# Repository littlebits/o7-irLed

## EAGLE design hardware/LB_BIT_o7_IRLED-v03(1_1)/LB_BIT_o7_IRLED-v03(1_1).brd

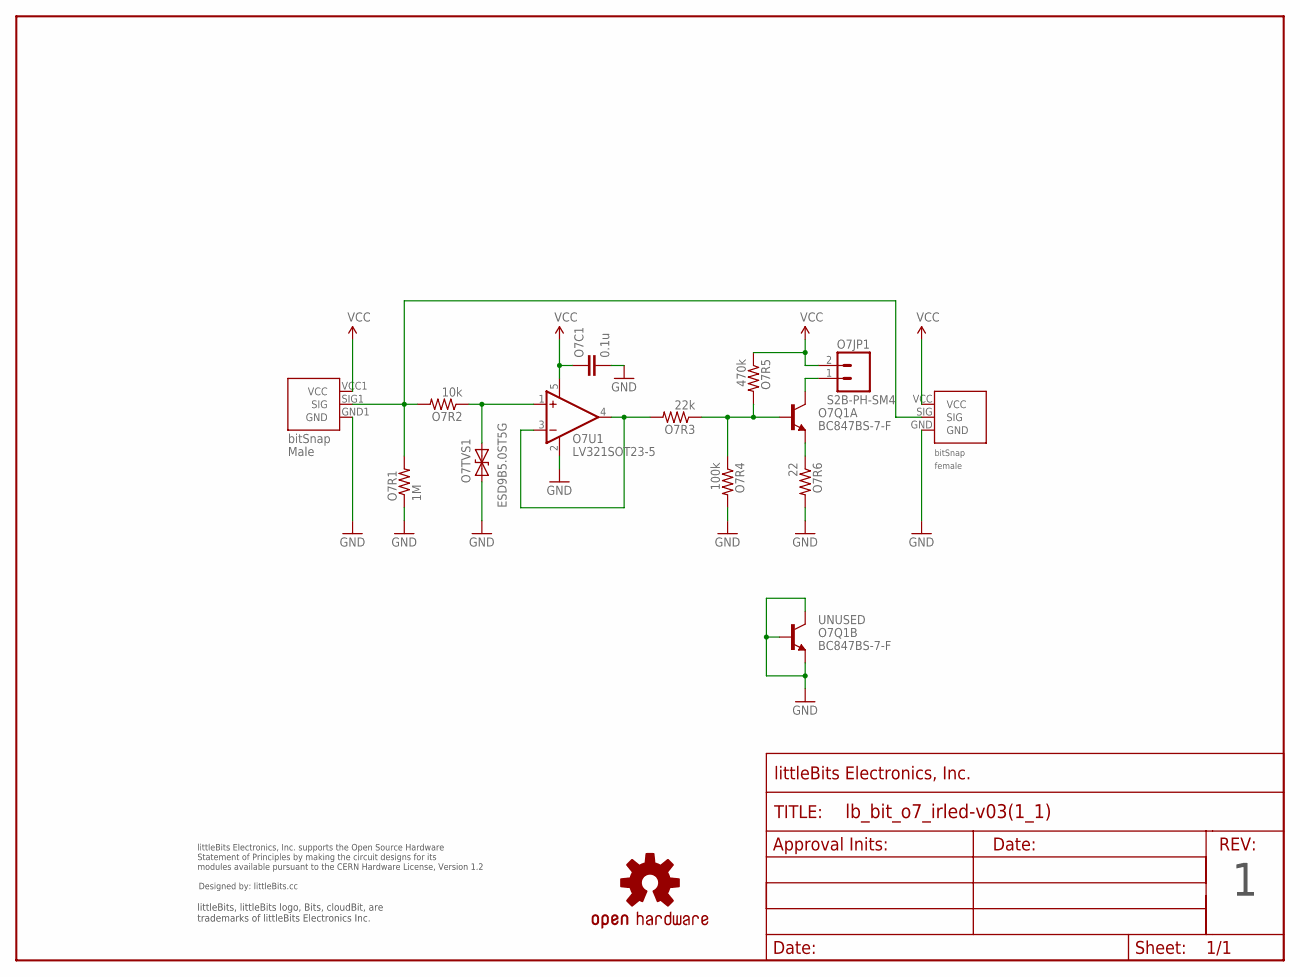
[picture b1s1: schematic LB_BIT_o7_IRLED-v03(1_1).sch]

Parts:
O7BSF1: BITSNAP_V03_FEMALE
O7BSM1: BITSNAP_V03_MALE
O7C1: 0.1u; CAP-0603
O7JP1: S2B-PH-SM4; S2B-PH
O7Q1: BC847BS-7-F; SOT-363_PHILLIPS
O7R1: 1M; RES-0603
O7R2: 10k; RES-0603
O7R3: 22k; RES-0603
O7R4: 100k; RES-0603
O7R5: 470k; RES-0603
O7R6: 22; RES-0603
O7TVS1: ESD9B5.0ST5G; SOD-923
O7U1: LV321SOT23-5; SOT23-5
U$5: FRAME-LETTER-OHWOHW; FABDWG01-OHW
U$8: OSHWCREDIT
U$14: OSHW-LOGOL; OSHW-LOGO-L

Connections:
GND: O7BSF1.GND, O7BSM1.GND1 (GND), O7C1.2, O7Q1.3 (C), O7Q1.4 (E), O7Q1.5 (B), O7R1.1, O7R4.2, O7R6.2, O7TVS1.1 (A), O7U1.2 (V-)
unnamed: O7JP1.1, O7Q1.6 (C)
unnamed: O7Q1.1 (E), O7R6.1
unnamed: O7Q1.2 (B), O7R3.1, O7R4.1, O7R5.2
unnamed: O7R2.1, O7TVS1.2 (C), O7U1.1 (+IN)
unnamed: O7BSF1.SIG, O7BSM1.SIG1 (SIG), O7R1.2, O7R2.2
unnamed: O7R3.2, O7U1.3 (-IN), O7U1.4 (OUT)
VCC: O7BSF1.VCC, O7BSM1.VCC1 (VCC), O7C1.1, O7JP1.2, O7R5.1, O7U1.5 (V+)

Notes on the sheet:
UNUSED

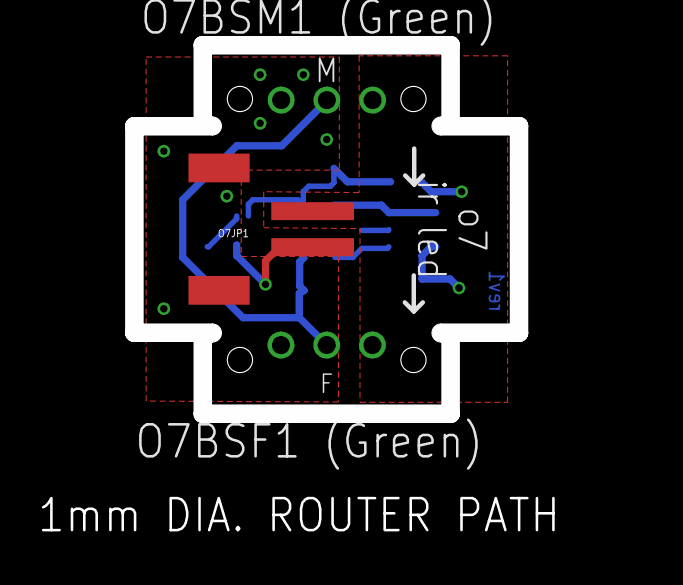
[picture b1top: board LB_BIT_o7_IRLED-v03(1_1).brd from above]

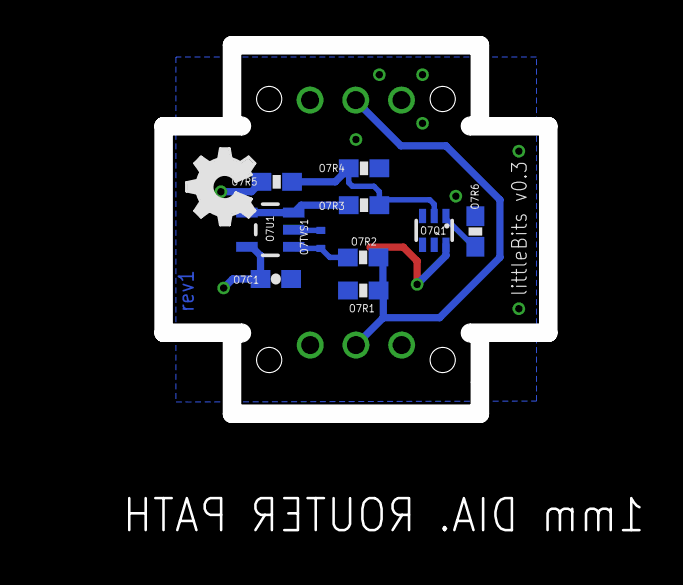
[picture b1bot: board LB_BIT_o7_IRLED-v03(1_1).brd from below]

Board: 2 copper layers, 32.9 x 27.5 mm, 18 parts (10 on the bottom side), 8 nets.

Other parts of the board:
DRILEGEND: DRILEGEND
U$7: OSHW_FILLX150_NOTEXT

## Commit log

2014-11-12 First commit, added hardware files
2014-11-12 Added readme

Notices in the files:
parts and their libraries:
LITTLEBITS: modules available pursuant to the CERN Hardware License,
Version 1.2
LITTLEBITS: modules available pursuant to the CERN Hardware License, Version 1.2
